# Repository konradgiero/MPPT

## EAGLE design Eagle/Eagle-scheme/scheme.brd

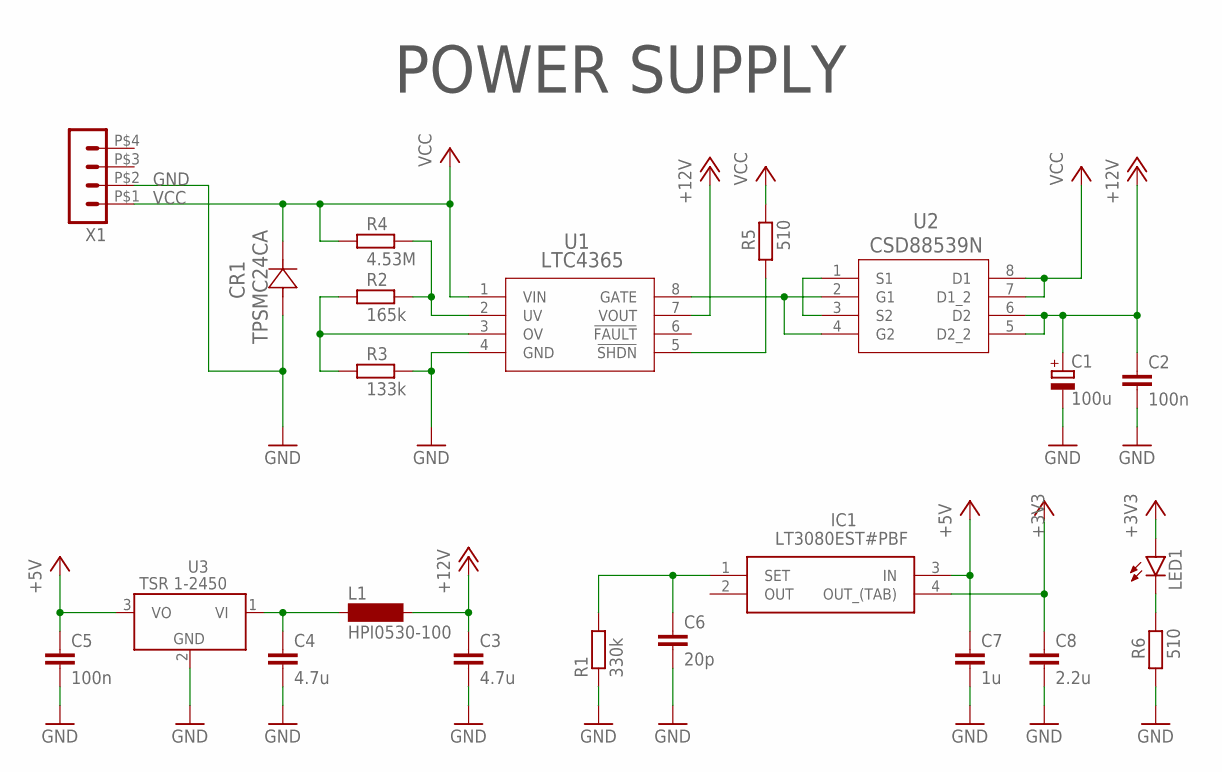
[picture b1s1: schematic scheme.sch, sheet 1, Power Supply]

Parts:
C1: 100u; UD-6,3X7,7_NICHICON
C2, C5: 100n; C0603K
C3, C4: 4.7u; C0805
C6: 20p; C0603K
C7: 1u; C0603
C8: 2.2u; C0603
CR1: TPSMC24CA; TPSMCSERIES-M
IC1: LT3080EST#PBF; SOT230P700X180-4N
L1: HPI0530-100; MS85
LED1: LEDCHIP-LED0805; CHIP-LED0805
R1: 330k; R0805
R2: 165k; R0603
R3: 133k; R0603
R4: 4.53M; R0603
R5, R6: 510; R0603
U1: LTC4365; TSOT-23_TS8-M
U2: CSD88539N; D8-M
U3: TSR 1-2450; TSR-1
X1: HEADER_POS4_43045-0401; 43045-0400

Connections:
+3V3: C8.1, IC1.4 (OUT_(TAB)), LED1.A; also elsewhere on the board
+5V: C5.1, C7.1, IC1.3 (IN), U3.3 (VO); also elsewhere on the board
+12V: C1.+, C2.1, C3.1, L1.2, U1.7 (VOUT), U2.5 (D2_2), U2.6 (D2); also elsewhere on the board
GND: C1.-, C2.2, C3.2, C4.2, C5.2, C6.2, C7.2, C8.2, CR1.2, R1.1, R3.1, R6.2, U1.4 (GND), U3.2 (GND), X1.P$2 (2); also elsewhere on the board
LTC_G: U1.8 (GATE), U2.2 (G1), U2.4 (G2)
unnamed: R2.1, R3.2, U1.3 (OV)
unnamed: R5.2, U1.5 (!SHDN)
unnamed: R2.2, R4.1, U1.2 (UV)
unnamed: U2.1 (S1), U2.3 (S2)
unnamed: C6.1, IC1.1 (SET), R1.2
unnamed: LED1.C, R6.1
VCC: CR1.1, R4.2, R5.1, U1.1 (VIN), U2.7 (D1_2), U2.8 (D1), X1.P$1 (1)
VI: C4.1, L1.1, U3.1 (VI)

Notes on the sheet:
POWER SUPPLY

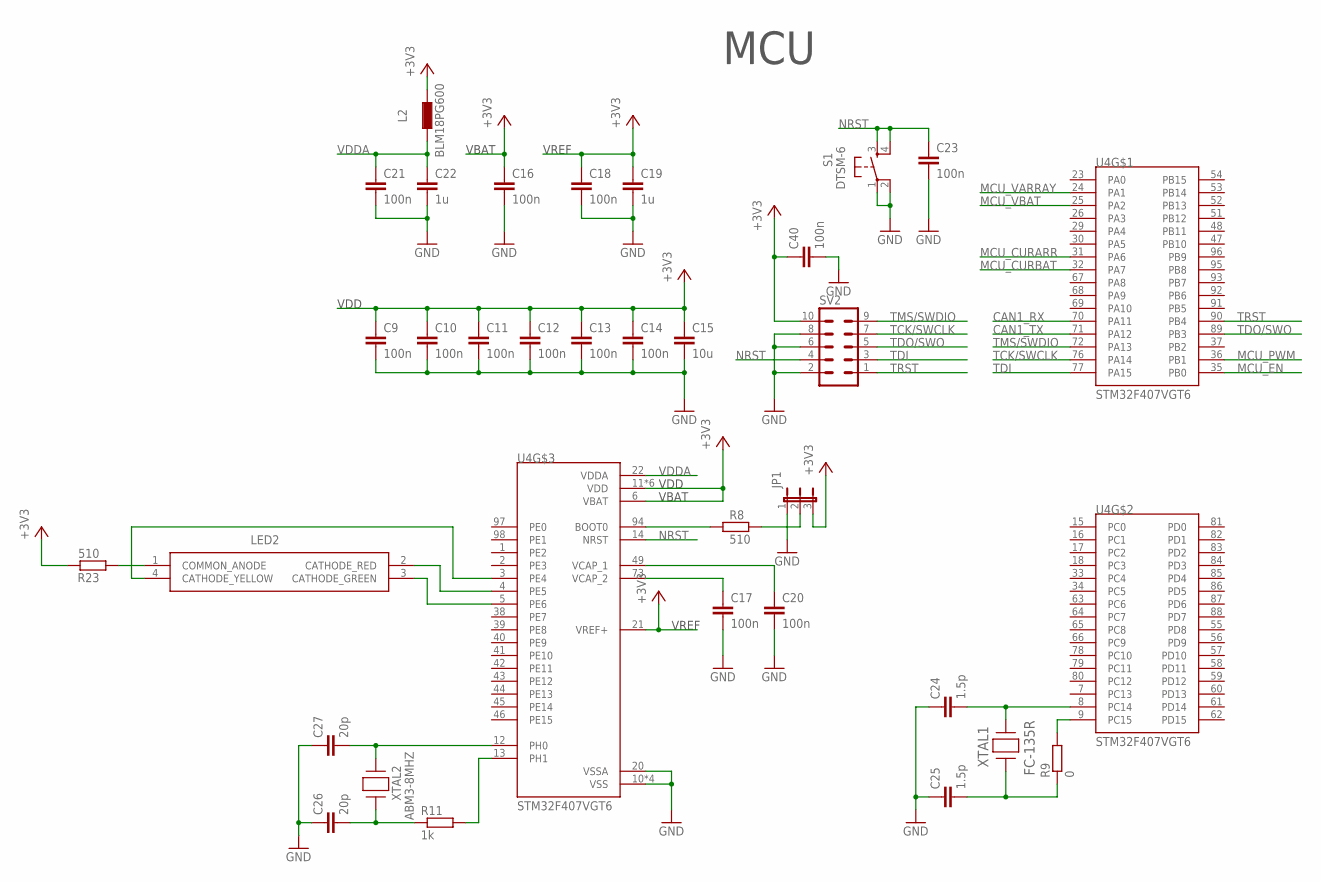
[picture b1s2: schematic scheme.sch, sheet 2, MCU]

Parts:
C9, C10, C11, C12, C13, C14, C16, C17, C18, C20, C21, C23: 100n; C0603K
C15: 10u; C0603K
C19, C22: 1u; C0603
C24, C25: 1.5p; C0603K
C26, C27: 20p; C0603K
C40: 100n; C0805K
JP1: JP2E; JP2
L2: BLM18PG600; L1608
LED2: APTF1616SURKCGKSYKC; KPTF1616RGBC11
R8, R23: 510; R0603
R9: 0; R0603
R11: 1k; R0603
S1: DTSM-6
SV2: ML10
U4: STM32F407VGT6; QFP50P1600X1600X160-100N
XTAL1: FC-135R; XTAL_KA-A3
XTAL2: ABM3-8MHZ; ABM38000MHZD2YT

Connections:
+3V3: C9.1, C10.1, C11.1, C12.1, C13.1, C14.1, C15.1, C16.1, C18.1, C19.1, C40.1, JP1.3, L2.2, R23.1, SV2.10, U4.6 (VBAT), U4.11 (VDD), U4.19 (VDD), U4.21 (VREF+), U4.28 (VDD), U4.50 (VDD), U4.75 (VDD), U4.100 (VDD); also elsewhere on the board
CAN1_RX: U4.70 (PA11); also elsewhere on the board
CAN1_TX: U4.71 (PA12); also elsewhere on the board
GND: C9.2, C10.2, C11.2, C12.2, C13.2, C14.2, C15.2, C16.2, C17.2, C18.2, C19.2, C20.2, C21.2, C22.2, C23.2, C24.1, C25.1, C26.1, C27.1, C40.2, JP1.1, S1.1, S1.2, SV2.2, SV2.6, SV2.8, U4.10 (VSS), U4.20 (VSSA), U4.27 (VSS), U4.74 (VSS), U4.99 (VSS); also elsewhere on the board
MCU_CURARR: U4.31 (PA6); also elsewhere on the board
MCU_CURBAT: U4.32 (PA7); also elsewhere on the board
MCU_EN: U4.35 (PB0); also elsewhere on the board
MCU_PWM: U4.36 (PB1); also elsewhere on the board
MCU_VARRAY: U4.24 (PA1); also elsewhere on the board
MCU_VBAT: U4.25 (PA2); also elsewhere on the board
unnamed: C26.2, R11.1, XTAL2.1
unnamed: C17.1, U4.73 (VCAP_2)
unnamed: C20.1, U4.49 (VCAP_1)
unnamed: R8.1, U4.94 (BOOT0)
unnamed: JP1.2, R8.2
unnamed: C25.2, R9.1, XTAL1.1
unnamed: R9.2, U4.9 (PC15)
unnamed: C24.2, U4.8 (PC14), XTAL1.2
unnamed: C27.2, U4.12 (PH0), XTAL2.2
unnamed: R11.2, U4.13 (PH1)
unnamed: LED2.1 (COMMON_ANODE), R23.2
unnamed: LED2.3 (CATHODE_GREEN), U4.5 (PE6)
unnamed: LED2.2 (CATHODE_RED), U4.4 (PE5)
unnamed: LED2.4 (CATHODE_YELLOW), U4.3 (PE4)
NRST: C23.1, S1.3, S1.4, SV2.4, U4.14 (NRST)
TCK/SWCLK: SV2.7, U4.76 (PA14)
TDI: SV2.3, U4.77 (PA15)
TDO/SWO: SV2.5, U4.89 (PB3)
TMS/SWDIO: SV2.9, U4.72 (PA13)
TRST: SV2.1, U4.90 (PB4)
VDDA: C21.1, C22.1, L2.1, U4.22 (VDDA)

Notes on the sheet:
MCU
VREF
VDD
VBAT

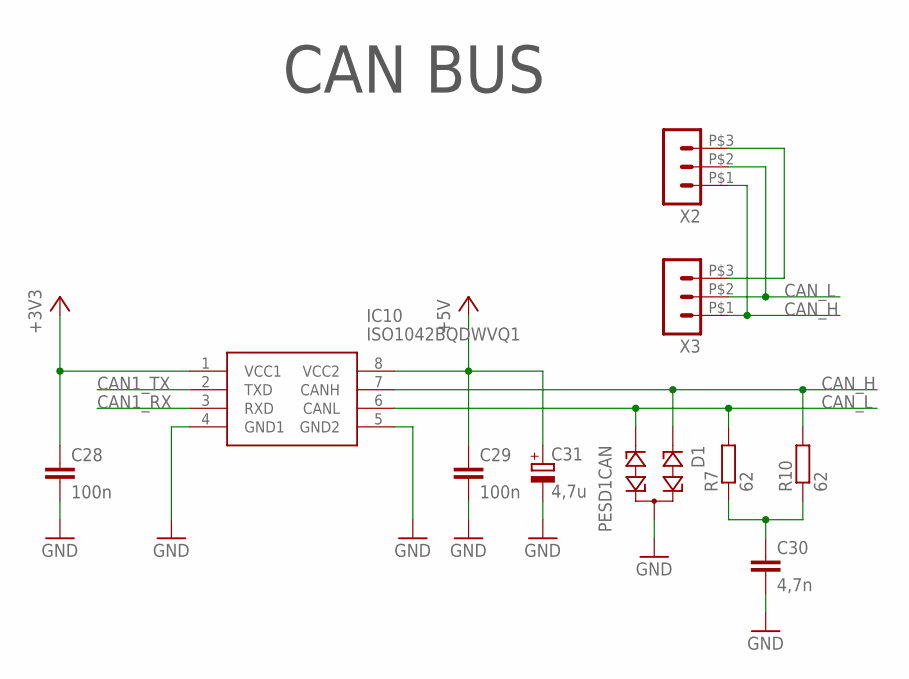
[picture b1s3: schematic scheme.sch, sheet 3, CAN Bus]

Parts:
C28, C29: 100n; C0603K
C30: 4,7n; C0603K
C31: 4,7u; UD-4X5,8_NICHICON
D1: PESD1CAN; SOT23
IC10: ISO1042BQDWVQ1; SOIC127P1150X280-8N
R7, R10: 62; R0603
X2, X3: HEADER_POS3_43650-0300; 43650-0300

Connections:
+3V3: C28.1, IC10.1 (VCC1); also elsewhere on the board
+5V: C29.1, C31.+, IC10.8 (VCC2); also elsewhere on the board
CAN1_RX: IC10.3 (RXD); also elsewhere on the board
CAN1_TX: IC10.2 (TXD); also elsewhere on the board
CAN_H: D1.1, IC10.7 (CANH), R10.2, X2.P$1 (1), X3.P$1 (1)
CAN_L: D1.2, IC10.6 (CANL), R7.2, X2.P$2 (2), X3.P$2 (2)
GND: C28.2, C29.2, C30.2, C31.-, D1.3, IC10.4 (GND1); also elsewhere on the board
unnamed: C30.1, R7.1, R10.1
unnamed: X2.P$3 (3), X3.P$3 (3)

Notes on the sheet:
CAN BUS

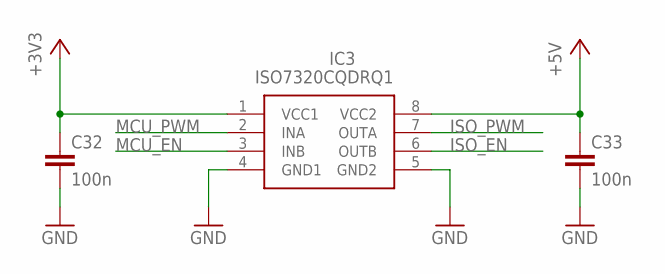
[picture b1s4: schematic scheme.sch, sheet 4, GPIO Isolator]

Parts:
C32, C33: 100n; C0603K
IC3: ISO7320CQDRQ1; SOIC127P600X175-8N

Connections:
+3V3: C32.1, IC3.1 (VCC1); also elsewhere on the board
+5V: C33.1, IC3.8 (VCC2); also elsewhere on the board
GND: C32.2, C33.2, IC3.4 (GND1), IC3.5 (GND2); also elsewhere on the board
ISO_EN: IC3.6 (OUTB); also elsewhere on the board
ISO_PWM: IC3.7 (OUTA); also elsewhere on the board
MCU_EN: IC3.3 (INB); also elsewhere on the board
MCU_PWM: IC3.2 (INA); also elsewhere on the board

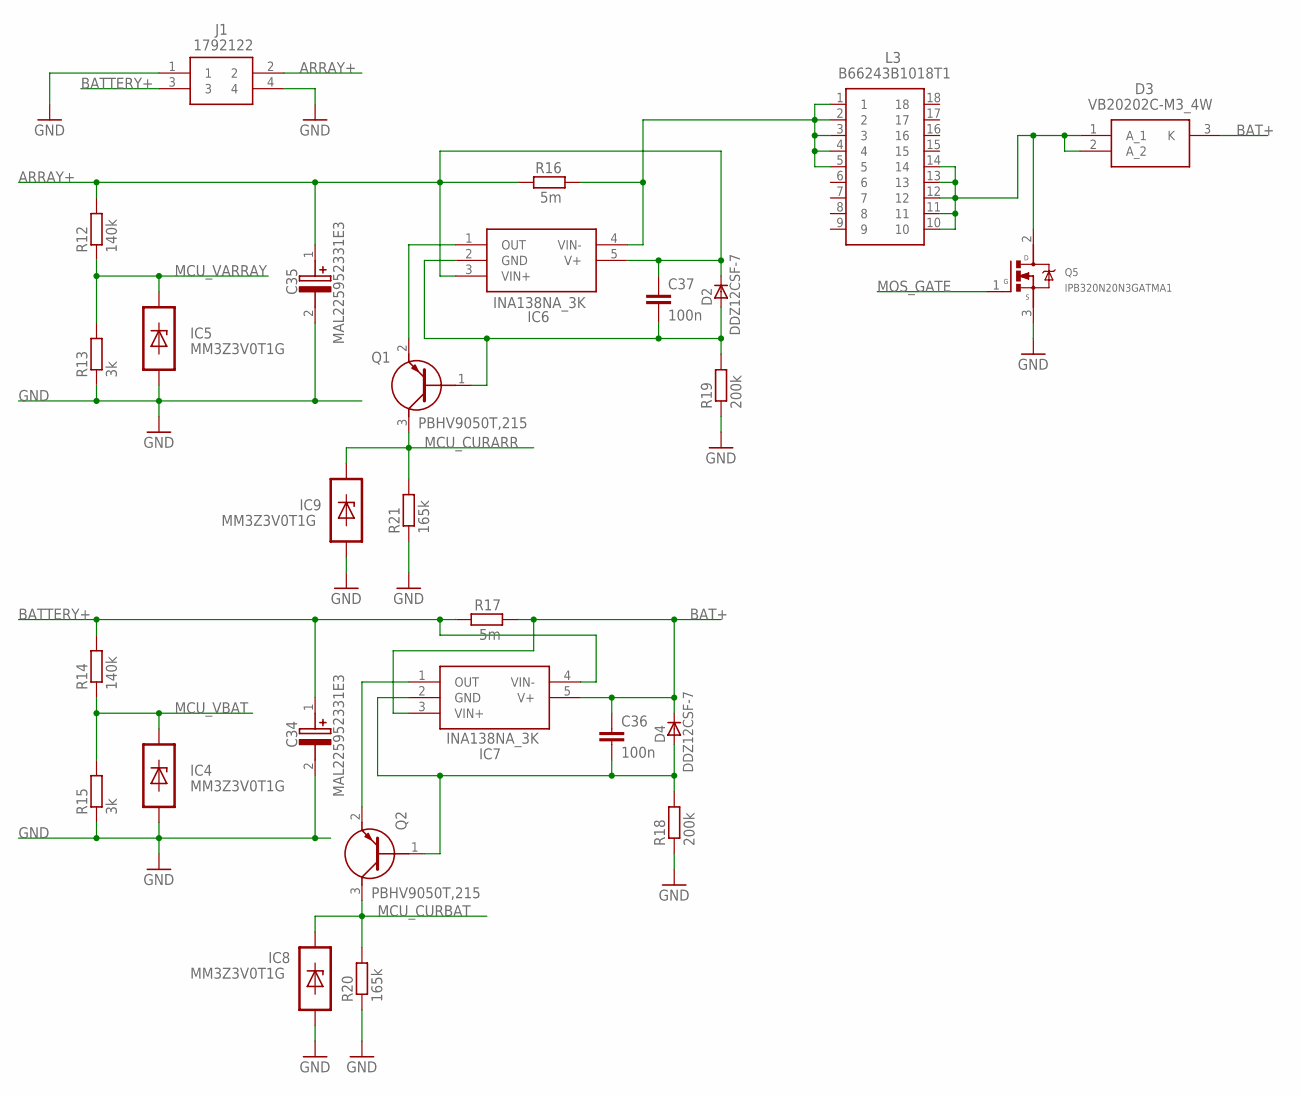
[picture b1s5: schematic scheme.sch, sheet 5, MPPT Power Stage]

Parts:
C34, C35: MAL225952331E3; CAPPRD1000W200D2200H3000
C36, C37: 100n; C0603K
D2, D4: DDZ12CSF-7; SOD323F
D3: VB20202C-M3_4W; VB20202CM34W
IC4, IC5, IC8, IC9: MM3Z3V0T1G; SOD323
IC6, IC7: INA138NA_3K; SOT95P280X145-5N
J1: 1792122
L3: B66243B1018T1; DIPS2750W100P500L4600H4140Q18N
Q1, Q2: PBHV9050T,215; SOT95P230X110-3N
Q5: IPB320N20N3GATMA1; DPAK508P1524X483-3N
R12, R14: 140k; R0603
R13, R15: 3k; R0603
R16, R17: 5m; R2512
R18, R19: 200k; R0805
R20, R21: 165k; R0805

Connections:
ARRAY+: C35.1 (+), C37.1, D2.C, IC6.3 (VIN+), IC6.5 (V+), J1.2, R12.2, R16.1
BAT+: C36.1, D3.3 (K), D4.C, IC7.3 (VIN+), IC7.5 (V+), R17.2
BATTERY+: C34.1 (+), IC7.4 (VIN-), J1.3, R14.2, R17.1
GND: C34.2 (-), C35.2 (-), IC4.2, IC5.2, IC8.2, IC9.2, J1.1, J1.4, Q5.3 (S), R13.1, R15.1, R18.1, R19.1, R20.1, R21.1; also elsewhere on the board
MCU_CURARR: IC9.1, Q1.3 (C), R21.2; also elsewhere on the board
MCU_CURBAT: IC8.1, Q2.3 (C), R20.2; also elsewhere on the board
MCU_VARRAY: IC5.1, R12.1, R13.2; also elsewhere on the board
MCU_VBAT: IC4.1, R14.1, R15.2; also elsewhere on the board
MOS_GATE: Q5.1 (G); also elsewhere on the board
unnamed: IC6.4 (VIN-), L3.1, L3.2, L3.3, L3.4, L3.5, R16.2
unnamed: D3.1 (A_1), D3.2 (A_2), L3.10, L3.11, L3.12, L3.13, L3.14, Q5.2 (D)
unnamed: IC7.1 (OUT), Q2.2 (E)
unnamed: IC6.1 (OUT), Q1.2 (E)
unnamed: C36.2, D4.A, IC7.2 (GND), Q2.1 (B), R18.2
unnamed: C37.2, D2.A, IC6.2 (GND), Q1.1 (B), R19.2

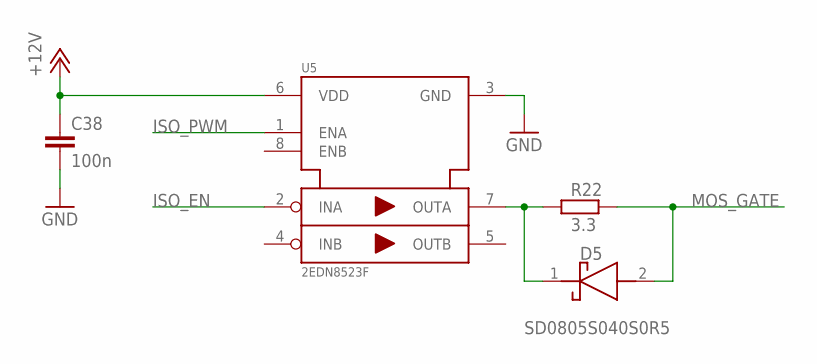
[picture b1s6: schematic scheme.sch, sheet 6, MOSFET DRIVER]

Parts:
C38: 100n; C0603K
D5: SD0805S040S0R5; SD0805
R22: 3.3; R0805
U5: 2EDN8523F; SOIC127P602X173-8N-V

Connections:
+12V: C38.1, U5.6 (VDD); also elsewhere on the board
GND: C38.2, U5.3 (GND); also elsewhere on the board
ISO_EN: U5.2 (INA); also elsewhere on the board
ISO_PWM: U5.1 (ENA); also elsewhere on the board
MOS_GATE: D5.2 (A), R22.2; also elsewhere on the board
unnamed: D5.1 (K), R22.1, U5.7 (OUTA)

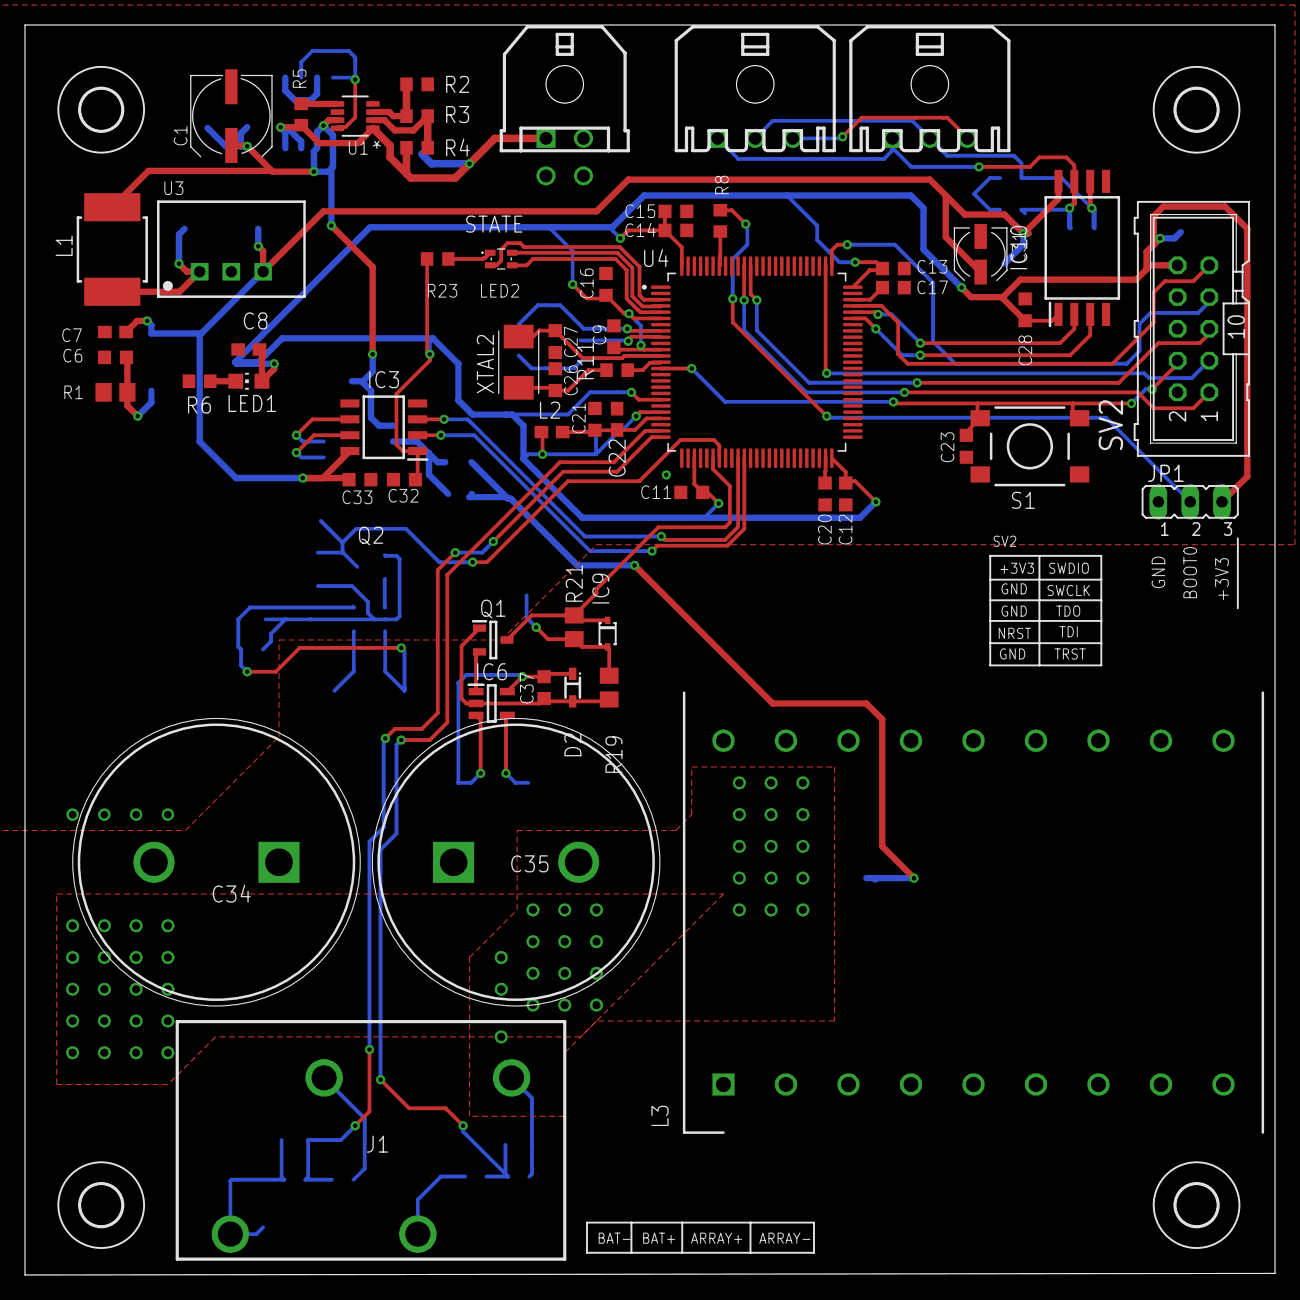
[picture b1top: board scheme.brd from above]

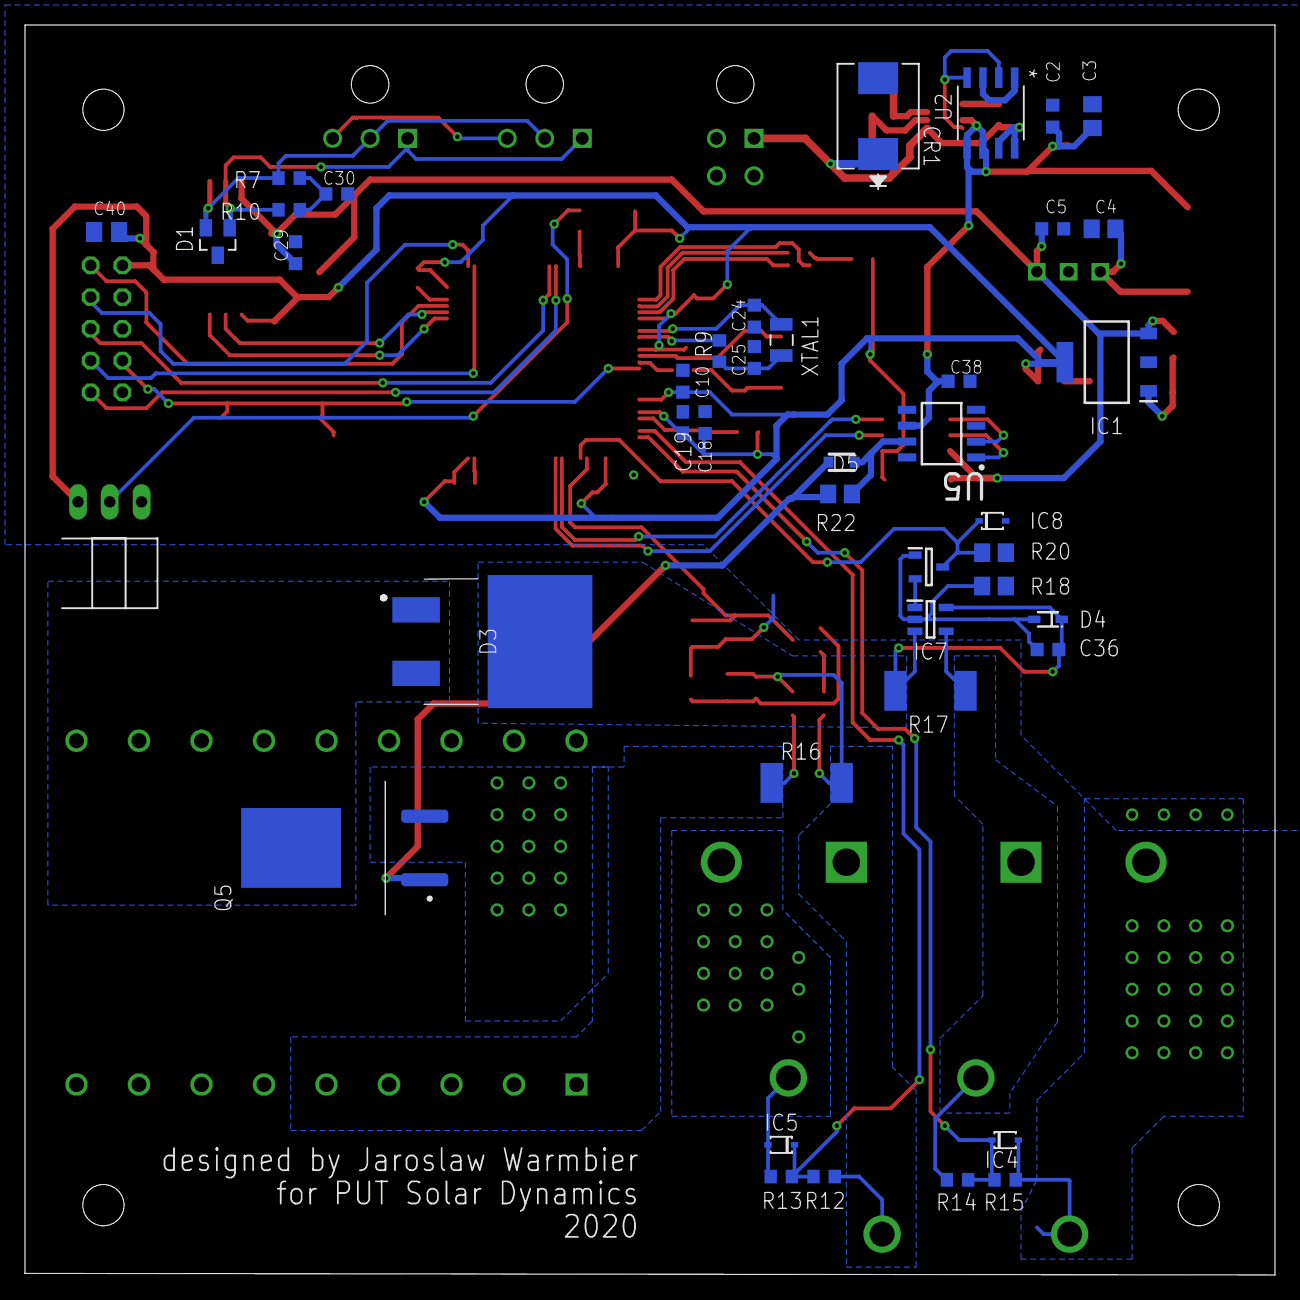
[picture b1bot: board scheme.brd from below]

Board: 2 copper layers, 100.0 x 100.0 mm, 103 parts (41 on the bottom side), 59 nets.

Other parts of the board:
U$1, U$2, U$3, U$4: 3,3

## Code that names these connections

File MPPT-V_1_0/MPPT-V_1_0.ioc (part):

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Mcu.Name=STM32F407V(E-G)Tx
Mcu.Package=LQFP100
Mcu.UserName=STM32F407VGTx
PA1.Signal=ADCx_IN1
PA11.GPIOParameters=GPIO_PuPd
PA11.GPIO_PuPd=GPIO_PULLDOWN
PA11.Mode=CAN_Activate
PA11.Signal=CAN1_RX
PA12.Mode=CAN_Activate
PA12.Signal=CAN1_TX
PA2.Signal=ADCx_IN2
PA6.Signal=ADCx_IN6
PA7.Signal=ADCx_IN7
PB0.Signal=GPIO_Output
PB1.Signal=S_TIM3_CH4
PC14-OSC32_IN.Mode=LSE-External-Oscillator
PC14-OSC32_IN.Signal=RCC_OSC32_IN
PC15-OSC32_OUT.Mode=LSE-External-Oscillator
PC15-OSC32_OUT.Signal=RCC_OSC32_OUT
PE4.Signal=GPIO_Output
PE5.Signal=GPIO_Output
PE6.Signal=GPIO_Output
PH0-OSC_IN.Mode=HSE-External-Oscillator
PH0-OSC_IN.Signal=RCC_OSC_IN
PH1-OSC_OUT.Mode=HSE-External-Oscillator
PH1-OSC_OUT.Signal=RCC_OSC_OUT
RCC.HSE_VALUE=25000000
RCC.SYSCLKFreq_VALUE=168000000
RCC.SYSCLKSource=RCC_SYSCLKSOURCE_PLLCLK
board=custom

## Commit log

2020-08-14 Added gitignore file
2020-08-14 removed metadata directory
2020-08-14 revert removed metadata directory
2020-08-14 added led state control functions
2020-08-16 whole functionality implemented
2020-08-17 added datasheet in polish
2021-08-21 Experiment with gitignore
2021-09-01 Gitignore
2021-09-01 Projekt działający już po wprowadzonych zmianach. Do wyjaśniania na co zmienne które nie są nigdzie deklarowane
2021-09-01 Małe poprawki i obgadanie ważnej rzeczy. Do napisania moduł przesunięcia bitowego w funkcji prepareData(plik can.c) no i jakieś odwołanie dodanych również do dodania. Oprócz tego dodano jeszcze konfi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
2021-09-01 Dodano operację przesunięcia bitowego tak aby wartości były dobrze zapisywane do komórek wysyłanych w protokole CAN.
2021-09-02 Dodanie deklaracji zmiennych których wcześniej brakowało w programie do poprawnego działania
2021-09-08 New clock config
    Zmieniono konfigurację tak żeby dokładnie odpowiadała boudrate'owi
2021-09-08 Init
    Initialize new branch
2021-09-08 Revert "Init"
    This reverts commit 62894a5d533fa5bcd588f3b74427696e704e5cdb.

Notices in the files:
parts and their libraries:
COPYRIGHT: Copyright (C) 2018 Accelerated Designs. All rights reserved
